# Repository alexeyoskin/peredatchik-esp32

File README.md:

# Передатчик на ESP32 — проект печатной платы в KiCad

Выполнил: Оськин А.А., группа БМТ2-31М  
Кафедра БМТ-2, МГТУ им. Н.Э. Баумана  
Проверил: Рязанцев П.

Репозиторий: https://github.com/alexeyoskin/peredatchik-esp32

## Задание

Создать проект печатной платы в KiCad. Проект должен содержать:

1. Библиотеку компонентов (УГО и посадочные места). УГО оформлены по ГОСТ, библиотека подключается к проекту как git-сабмодуль, пути к библиотекам относительные.
2. Схему электрическую принципиальную по ГОСТ с рамкой и основной надписью. Важные цепи описаны в классах цепей. У компонентов есть поле `Manufacturer\_Part\_Number` с реальным партномером.
3. Файл печатной платы, разведённый с учётом технологических возможностей завода Резонит (DFMA).
4. Скрипт, который делает проверку ERC и DRC, генерирует gerber-файлы, BOM и pdf-версию схемы.

## Описание устройства

Передатчик собран на модуле ESP32-WROOM-32 и питается от Li-ion аккумулятора 18650.

|Узел|Компоненты|Назначение|
|-|-|-|
|Питание от USB|XS1 (USB Type-C)|5 В для зарядки|
|Заряд аккумулятора|DA1 (TP4054), HL1|контроллер заряда, светодиод показывает заряд|
|Стабилизатор|DA3 (XC6206, LDO 3,3 В)|питание модуля|
|Сброс|DA2 (MAX809), VT2 (AO3400A)|супервизор питания|
|Измерение батареи|R8, R9|делитель, напряжение идёт на АЦП (VBAT\_ADC)|
|Управление|SB1–SB4|кнопки EN, BOOT и две пользовательские (BTN1, BTN2)|
|Звук|HA1 (зуммер), VT1|зуммер с ключом на транзисторе|
|Прошивка|XP1|разъём UART|

Проект выполнен в KiCad 10.

## Структура репозитория

```
peredatchik-esp32/
├── педальная с.kicad\_pro          проект
├── педальная с.kicad\_sch          схема Э3
├── педальная с.kicad\_pcb          печатная плата
├── sym-lib-table, fp-lib-table    таблицы библиотек (относительные пути)
├── lib/                           git-сабмодуль GOST\_ESKD
│   ├── GOST\_ESKD.kicad\_sym        УГО по ГОСТ
│   ├── GOST\_ESKD.pretty/          посадочные места
│   └── GOST\_form1.kicad\_wks       рамка и основная надпись
├── kicad\_project\_processing.bat   скрипт проверки и выпуска (Windows)
├── kicad\_project\_processing.sh    то же для Linux
├── docs/                          картинки для отчёта
└── README.md / README.pdf         отчёт
```

## 1\. Библиотека компонентов

Библиотека лежит в отдельном репозитории `GOST\_ESKD`. В проект она подключена как сабмодуль в папку `lib`:

```
git submodule add https://github.com/alexeyoskin/GOST\_ESKD.git lib
```

Таблицы библиотек проекта используют переменную `${KIPRJMOD}` (папка проекта), поэтому абсолютных путей нет и проект открывается на любом компьютере:

```
(lib (name "GOST\_ESKD")(type "KiCad")(uri "${KIPRJMOD}/lib/GOST\_ESKD.kicad\_sym"))
(lib (name "GOST\_ESKD")(type "KiCad")(uri "${KIPRJMOD}/lib/GOST\_ESKD.pretty"))
```

Путь к рамке в настройках проекта задан так же: `${KIPRJMOD}/lib/GOST\_form1.kicad\_wks`.

### УГО

Все символы нарисованы в миллиметрах, выводы стоят на сетке 2,5 мм, шрифт 2,5 мм. Размеры взяты из ГОСТ:

|Элемент|ГОСТ|Размеры|
|-|-|-|
|Резистор R|2.728|4 × 10 мм|
|Конденсатор C|2.728|обкладки 8 мм, зазор 1,5 мм|
|Светодиод HL|2.730|диод в круге Ø10, стрелки под 45°|
|Транзисторы VT|2.730|круг Ø12 мм|
|Кнопка SB|2.755|разрыв 6 мм, наклон 30°|
|Элемент G|2.742|пластины 8 и 4 мм, зазор 1,5 мм|
|Зуммер HA|2.741|—|
|Микросхемы DA, модуль A|2.743|основное и дополнительные поля, шаг выводов 5 мм|
|Разъёмы XS, XP|2.755|таблица «Конт. / Цепь»|

Позиционные обозначения даны по ГОСТ 2.710. Нумерация выводов совпадает с корпусами. Для SOT-23 разные варианты цоколёвки сделаны отдельными символами (например, `NMOS\_DGS`, `NPN\_CBE`).

!\[УГО, использованные в схеме](docs/ugo.png)

### Посадочные места

В `GOST\_ESKD.pretty` собраны все 13 посадочных мест платы. Это корпуса 1206, SOT-23/SOT-23-5, LED 0402, электролиты D5 мм, кнопки, штыревые разъёмы, USB-C GCT USB4135, зуммер и модуль ESP32-WROOM-32. Все компоненты на схеме и на плате ссылаются на библиотеку `GOST\_ESKD`.

## 2\. Схема электрическая принципиальная

Схема нарисована на одном листе формата А3. Рамка `GOST\_form1.kicad\_wks` сделана по ГОСТ 2.301 и ГОСТ 2.104 (форма 1):

* поля 20/5/5/5 мм;
* основная надпись 185 × 55 мм;
* дополнительные графы 19–23 и 26.

Поля надписи заполняются в *Файл → Параметры страницы*. Обозначение схемы: БИГЕ.941239.001 Э3.

!\[Схема электрическая принципиальная](docs/schematic.png)

### Классы цепей

Важные цепи распределены по классам цепей (*Параметры схемы → Классы цепей*) и выделены цветом.

|Класс|Цвет|Цепи|
|-|-|-|
|Power|красный|/VBUS, /VBAT|
|Power\_3V3|оранжевый|/+3V3|
|GND|синий|GND, /GND\_BAT|
|Signal|зелёный|/UART\_TX, /UART\_RX, /ESP\_EN, /BOOT, /RESET\_N, /BTN1, /BTN2, /BUZZER, /VBAT\_ADC, /CHRG|

Цепи названы локальными метками, поэтому KiCad добавляет к их именам «/». С этим префиксом записаны и шаблоны классов.

### Партномера

У всех компонентов заполнено поле `Manufacturer\_Part\_Number`. Партномера подобраны на lcsc.com и в «Чип и Дип» так, чтобы корпус совпадал с посадочным местом.

|Поз. обозн.|Наименование|Корпус|Manufacturer\_Part\_Number|
|-|-|-|-|
|A1|Модуль ESP32|модуль|ESP32-WROOM-32E-N4|
|C1, C5, C6|10 мкФ|1206|CL31A106KAHNNNE|
|C2|4,7 мкФ|1206|CL31A475KAHNNNE|
|C3, C4|10 мкФ × 16 В|D5 мм|UVR1C100MDD|
|C7|1 мкФ|1206|CL31B105KBHNNNE|
|DA1|Контроллер заряда Li-ion|SOT-23-5|TP4054|
|DA2|Супервизор питания|SOT-23|MAX809SEUR+T|
|DA3|Стабилизатор 3,3 В|SOT-23|XC6206P332MR|
|G1|Аккумулятор 18650|—|INR18650-35E|
|HA1|Зуммер|12 × 12 мм|PKLCS1212E4001-R1|
|HL1|Светодиод зелёный|0402|APHHS1005CGCK|
|R1–R4, R6, R7, R9|1 кОм|1206|RC1206JR-071KL|
|R5|2 кОм|1206|RC1206JR-072KL|
|R8, R10–R12|10 кОм|1206|RC1206JR-0710KL|
|SB1, SB2|Кнопка тактовая|THT|MJTP1243|
|SB3, SB4|Штыревой разъём под выносную кнопку|1 × 2, 2,54 мм|61300211121|
|VT1|Транзистор NPN|SOT-23|MMBT3904|
|VT2|MOSFET N-канальный|SOT-23|AO3400A|
|XP1|Вилка UART|1 × 4, 2,54 мм|61300411121|
|XS1|Розетка USB Type-C|SMD|USB4135-GF-A|

Аккумулятор G1 стоит в держателе вне платы, поэтому он исключён из платы, но остаётся в BOM.

Результат ERC: 0 ошибок.

## 3\. Печатная плата

!\[Печатная плата, верхний слой](docs/pcb.png)

|Параметр|Значение|
|-|-|
|Размер платы|56,5 × 58 мм|
|Число слоёв|2|
|Толщина|1,6 мм|
|Мин. ширина проводника|0,2 мм (выводы ESP32), основные трассы 0,4 мм|
|Мин. зазор|0,2 мм|
|Переходные отверстия|0,6 / 0,3 мм|
|Мин. диаметр отверстия|0,2 мм|
|Мин. гарантийный поясок|0,1 мм|
|Зазор медь – край платы|0,5 мм|
|Крепёжные отверстия|4 × Ø3 мм по углам|
|Земля|полигоны GND на обоих слоях|

Нормы взяты с запасом относительно стандартных возможностей завода Резонит. Плату можно заказать как обычную двухслойную, без дополнительных опций.

Что сделано для технологичности (DFMA):

* все компоненты стоят на одной стороне (верхний слой). Так плату можно собрать за один проход;
* пассивные компоненты в основном одного корпуса 1206, ручная пайка тоже возможна;
* под антенной ESP32 оставлена зона без меди, модуль выходит антенной к краю платы;
* переходных отверстий всего 4, остальная разводка на верхнем слое;
* полигоны земли подключены к площадкам через термобарьеры;
* позиционные обозначения на шелкографии не заходят на площадки;
* разъёмы USB, UART и кнопки стоят у краёв платы.

Результат DRC: 0 ошибок, 0 неразведённых соединений, плата соответствует схеме.

## 4\. Скрипт

Скрипт `kicad\_project\_processing.bat` (для Windows) и `kicad\_project\_processing.sh` (для Linux) лежат в корне проекта и запускаются оттуда же. Имя проекта скрипт берёт из файла `.kicad\_pro`, все пути относительные, результаты складываются в папку `output/`.

|Шаг|Команда|Результат|
|-|-|-|
|ERC|`kicad-cli sch erc --severity-error --exit-code-violations`|`output/erc\_report.rpt`|
|DRC с проверкой соответствия схеме|`kicad-cli pcb drc --schematic-parity --refill-zones --severity-error --exit-code-violations`|`output/drc\_report.rpt`|
|PDF схемы|`kicad-cli sch export pdf -b`|`output/<проект>\_schematic.pdf`|
|BOM|`kicad-cli sch export bom` (поля: позиция, номинал, корпус, партномер, кол-во)|`output/<проект>\_BOM.csv`|
|Gerber|`kicad-cli pcb export gerbers` (слои Cu, Paste, Mask, Silkscreen, Edge.Cuts)|`output/gerbers/`|
|Сверловка|`kicad-cli pcb export drill --excellon-separate-th`|`output/gerbers/`|
|Архив для завода|zip папки `gerbers`|`output/<проект>\_gerbers.zip`|
|3D-модель|`kicad-cli pcb export step`|`output/<проект>.step`|

Если ERC или DRC находит ошибки, скрипт сообщает об этом и завершается с кодом 1.

## Итог

Сделано:

* библиотека УГО и посадочных мест, подключённая git-сабмодулем;
* схема по ГОСТ с рамкой, классами цепей и партномерами;
* двухслойная плата, проходящая ERC и DRC без ошибок;
* скрипт, который одной командой проверяет проект и выпускает gerber, BOM и pdf схемы.

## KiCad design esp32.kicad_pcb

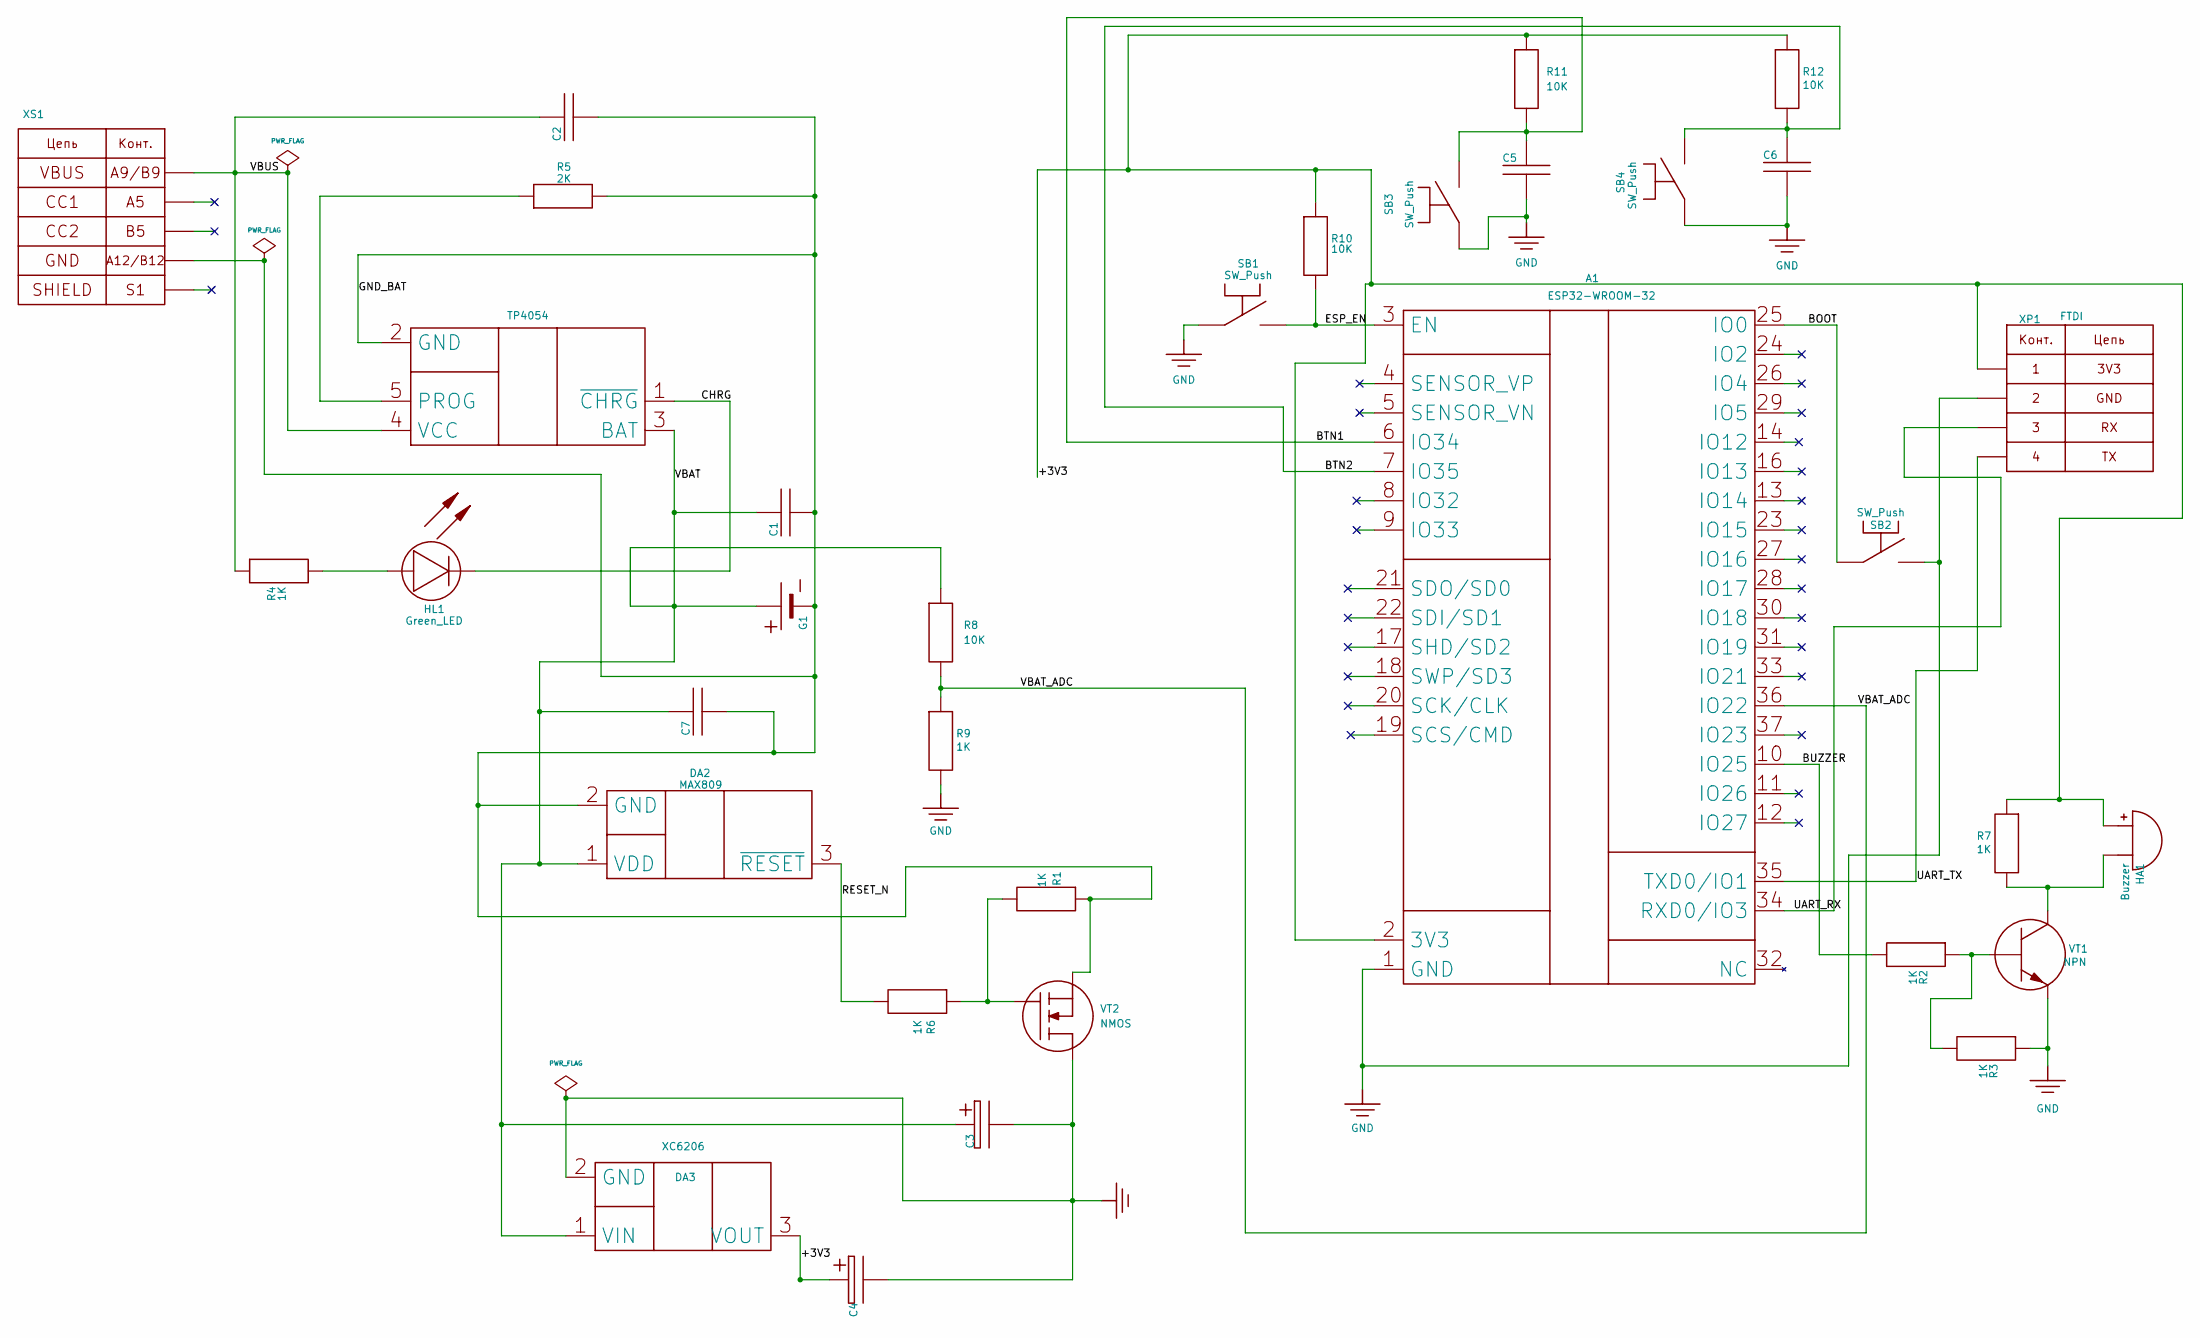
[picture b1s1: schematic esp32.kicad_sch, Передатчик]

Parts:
A1: ESP32-WROOM-32; Manufacturer_Part_Number ESP32-WROOM-32E-N4
C1, C5, C6: 1206 10mk 5%; C_1206_3216Metric_Pad1.33x1.80mm_HandSolder; Manufacturer_Part_Number CL31A106KAHNNNE
C2: 1206 4.7 мкФ 5%; C_1206_3216Metric_Pad1.33x1.80mm_HandSolder; Manufacturer_Part_Number CL31A475KAHNNNE
C3, C4: 10 мк × 16 В; CP_Radial_D5.0mm_P2.50mm; Manufacturer_Part_Number UVR1C100MDD
C7: 1206 1mk 5%; C_1206_3216Metric_Pad1.33x1.80mm_HandSolder; Manufacturer_Part_Number CL31B105KBHNNNE
DA1: TP4054; SOT-23-5; Manufacturer_Part_Number TP4054
DA2: MAX809; SOT-23-3; Manufacturer_Part_Number MAX809SEUR+T
DA3: XC6206; SOT-23; Manufacturer_Part_Number XC6206P332MR
G1: Battery_Cell; BatteryHolder_Keystone_1042_1x18650; Manufacturer_Part_Number INR18650-35E
HA1: Buzzer; Buzzer_Murata_PKLCS1212E; Manufacturer_Part_Number PKLCS1212E4001-R1
HL1: Green_LED; LED_0402_1005Metric; Manufacturer_Part_Number APHHS1005CGCK
R1, R2, R3, R4, R6, R7, R9: 1K; R_1206_3216Metric; Manufacturer_Part_Number RC1206JR-071KL
R5: 2K; R_1206_3216Metric; Manufacturer_Part_Number RC1206JR-072KL
R8, R10, R11, R12: 10K; R_1206_3216Metric; Manufacturer_Part_Number RC1206JR-0710KL
SB1, SB2: SW_Push; SW_PUSH_1P1T_6x3.5mm_H4.3_APEM_MJTP1243; Manufacturer_Part_Number MJTP1243
SB3, SB4: SW_Push; PinHeader_1x02_P2.54mm_Vertical; Manufacturer_Part_Number 61300211121
VT1: NPN; SOT-23-3; Manufacturer_Part_Number MMBT3904
VT2: NMOS; SOT-23-3; Manufacturer_Part_Number AO3400A
XP1: FTDI; PinHeader_1x04_P2.54mm_Vertical; Manufacturer_Part_Number 61300411121
XS1: USB_C_Receptacle_PowerOnly_6P; USB_C_Receptacle_GCT_USB4135-GF-A_6P_TopMnt_Horizontal; Manufacturer_Part_Number USB4135-GF-A

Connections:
/+3V3: A1.2 (3V3), C4.1 (+), DA3.3 (VOUT), HA1.1 (+), R7.1, R10.1, R11.1, R12.1, XP1.1 (3V3)
/BOOT: A1.25 (IO0), SB2.1
/BTN1: A1.6 (IO34), C5.1, R11.2, SB3.2
/BTN2: A1.7 (IO35), C6.1, R12.2, SB4.2
/BUZZER: A1.10 (IO25), R2.2
/CHRG: DA1.1 (~CHRG), HL1.1 (K)
/ESP_EN: A1.3 (EN), R10.2, SB1.2
/GND_BAT: C1.2, C2.2, C7.2, DA1.2 (GND), DA2.2 (GND), G1.2 (-), R1.1, R5.2, VT2.3 (S), XS1.A12 (GND), XS1.B12 (GND)
/RESET_N: DA2.3 (~RESET), R6.2
/UART_RX: A1.34 (RXD0/IO3), XP1.3 (RX)
/UART_TX: A1.35 (TXD0/IO1), XP1.4 (TX)
/VBAT: C1.1, C3.1 (+), C7.1, DA1.3 (BAT), DA2.1 (VDD), DA3.1 (VIN), G1.1 (+), R8.1
/VBAT_ADC: A1.36 (IO22), R8.2, R9.1
/VBUS: C2.1, DA1.4 (VCC), R4.1, XS1.A9 (VBUS), XS1.B9 (VBUS)
GND: A1.1 (GND), A1.15 (GND), A1.38 (GND), A1.39 (GND), C3.2 (-), C4.2 (-), C5.2, C6.2, DA3.2 (GND), R3.1, R9.2, SB1.1, SB2.2, SB3.1, SB4.1, VT1.3 (E), VT2.1 (D), XP1.2 (GND)
unnamed: DA1.5 (PROG), R5.1
unnamed: HA1.2 (-), R7.2, VT1.1 (C)
unnamed: HL1.2 (A), R4.2
unnamed: R2.1, R3.2, VT1.2 (B)
unnamed: R1.2, R6.1, VT2.2 (G)

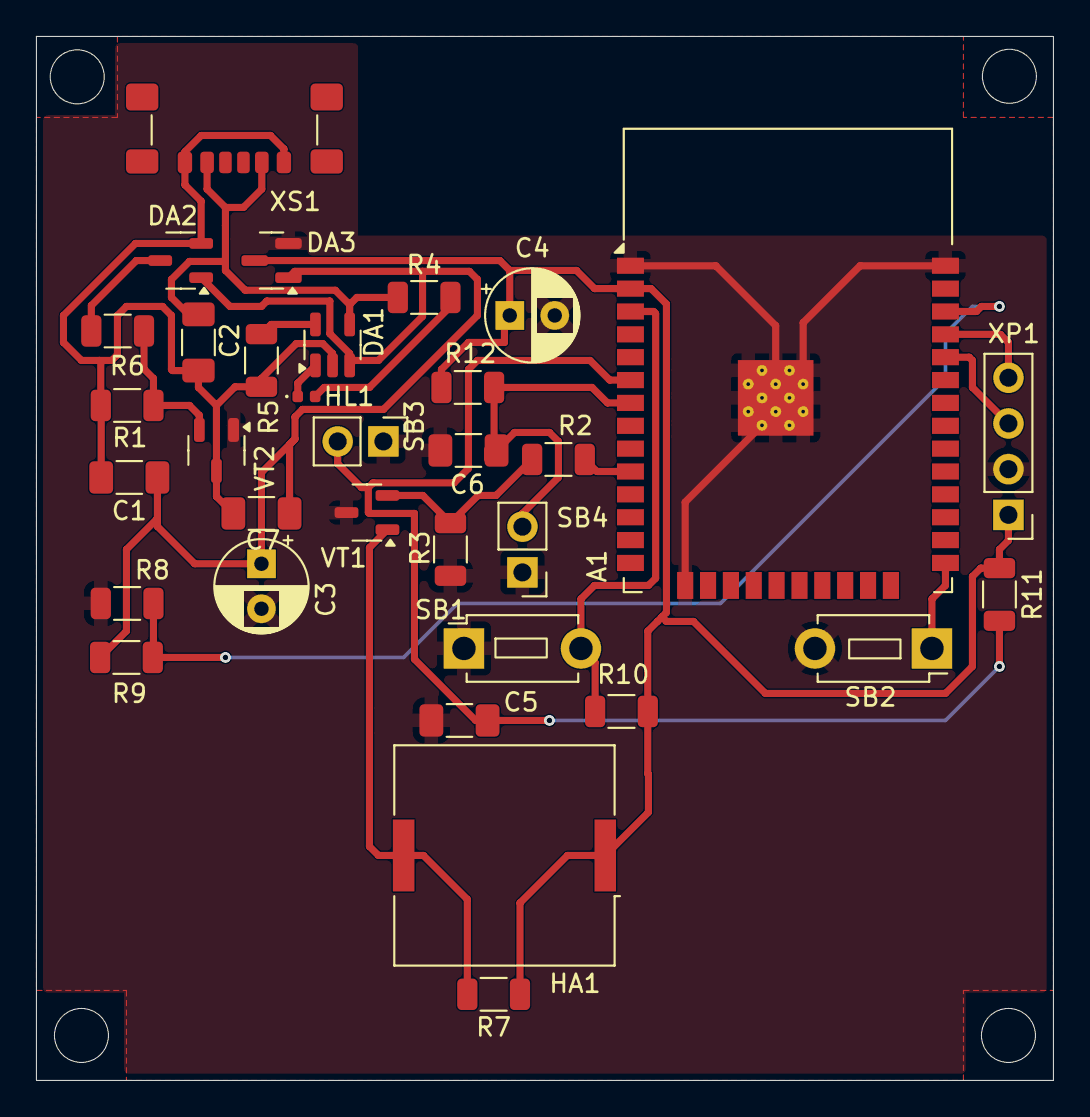
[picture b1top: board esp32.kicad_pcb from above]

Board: 2 copper layers, 56.5 x 58.0 mm, 33 parts (0 on the bottom side), 20 nets.
